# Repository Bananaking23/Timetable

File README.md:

# Timetable

This project is a useful thing, and it helped my 3d modelling skills.

I have made a new timetable using a Seeed XIAO nRF52840 as it has bluetooth and it is very small, a 1.54 inch epaper display, and an rgb led. It uses a lipo battery and a tp4056 to charge it. 
it is used by changing the subjects in the code and then turning it on, 2 buttons are for up and down, 1 for select, a switch to turn on/off

## Photos
### case+stand+pcb

### Case

### Stand

It connecsts to the case using a 2 pin pogo connector.

### Schematic

### PCB

## BOM

THIS IS WITHOUT DISCOUNTS BTW, i cant include discounts rn as they arent in my cart, just a wishlist, but it will be about 10-15 pounds less

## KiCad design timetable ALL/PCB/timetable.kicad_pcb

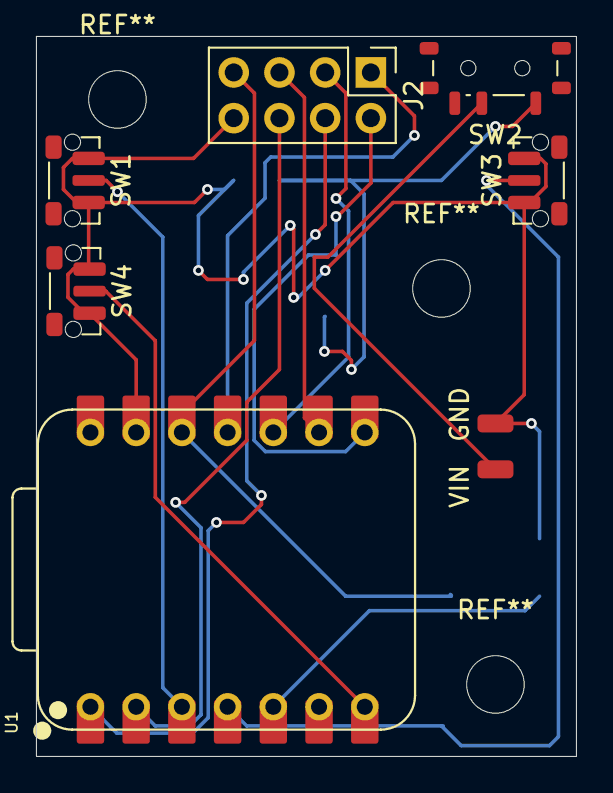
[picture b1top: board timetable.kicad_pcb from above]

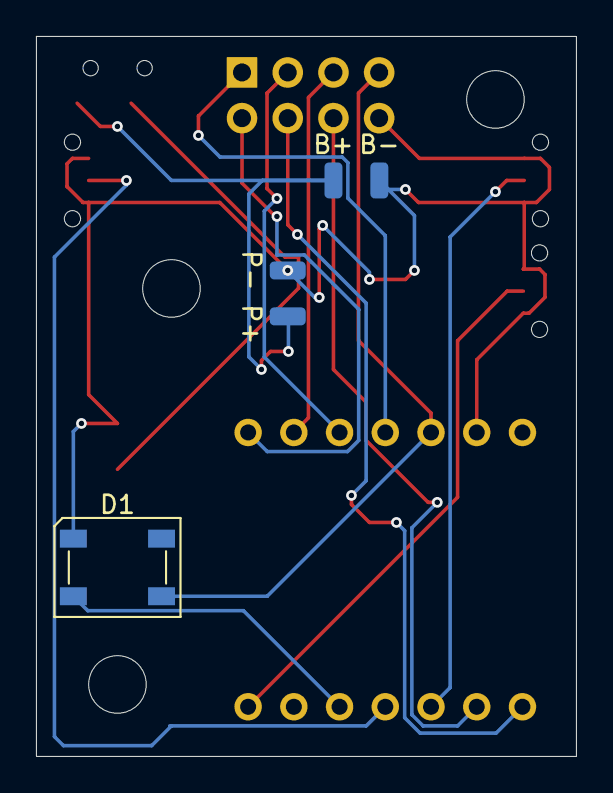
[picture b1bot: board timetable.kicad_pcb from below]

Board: 2 copper layers, 30.0 x 40.0 mm, 13 parts (5 on the bottom side), 14 nets.

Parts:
B+: B+; SolderWirePad_1x01_SMD_1x2mm
B-: B-; SolderWirePad_1x01_SMD_1x2mm
D1: SK6812; LED_SK6812_PLCC4_5.0x5.0mm_P3.2mm
GND: GND; SolderWirePad_1x01_SMD_1x2mm
J2: display connector; PinHeader_2x04_P2.54mm_Vertical
P+: P1; SolderWirePad_1x01_SMD_1x2mm
P-: P2; SolderWirePad_1x01_SMD_1x2mm
SW1, SW3, SW4: SW_Push; SW_Push_1P1T-MP_NO_Horizontal_Alps_SKRTLAE010
SW2: SW_SPDT; SW_SPDT_Shouhan_MSK12C02
U1: XIAO-RP2040-DIP
VIN: VIN; SolderWirePad_1x01_SMD_1x2mm

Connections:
+3.3V: D1.3 (VDD), J2.7, U1.12 (3V3)
GND: B-.1, D1.1 (VSS), GND.1, J2.8, P-.1, SW1.1, SW3.1, SW4.1, U1.13 (GND)
unnamed: B+.1, P+.1, SW2.1 (A)
unnamed: D1.2 (DIN), U1.5 (GPIO6/SDA)
unnamed: SW2.2 (B), VIN.1
b1: SW1.2, U1.3 (GPIO28/ADC2/A2)
b2: SW3.2, U1.4 (GPIO29/ADC3/A3)
b3: SW4.2, U1.7 (GPIO0/TX)
busy: J2.1, U1.11 (GPIO3/MOSI)
cs: J2.4, U1.1 (GPIO26/ADC0/A0)
d/c: J2.3, U1.10 (GPIO4/MISO)
res: J2.2, U1.8 (GPIO1/RX)
scl/clk: J2.5, U1.9 (GPIO2/SCK)
sda/din: J2.6, U1.2 (GPIO27/ADC1/A1)

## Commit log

2026-01-31 Update README with discount information
    Added a note about discounts to the BOM section.
2026-01-31 Update README with usage instructions
    Added usage instructions for the timetable project.
2026-01-31 Update README with button functionality details
    Added details about the buttons for navigation and power switch.
2026-02-24 Refactor CSV formatting and remove empty lines
    Removed empty lines and adjusted formatting in CSV.
